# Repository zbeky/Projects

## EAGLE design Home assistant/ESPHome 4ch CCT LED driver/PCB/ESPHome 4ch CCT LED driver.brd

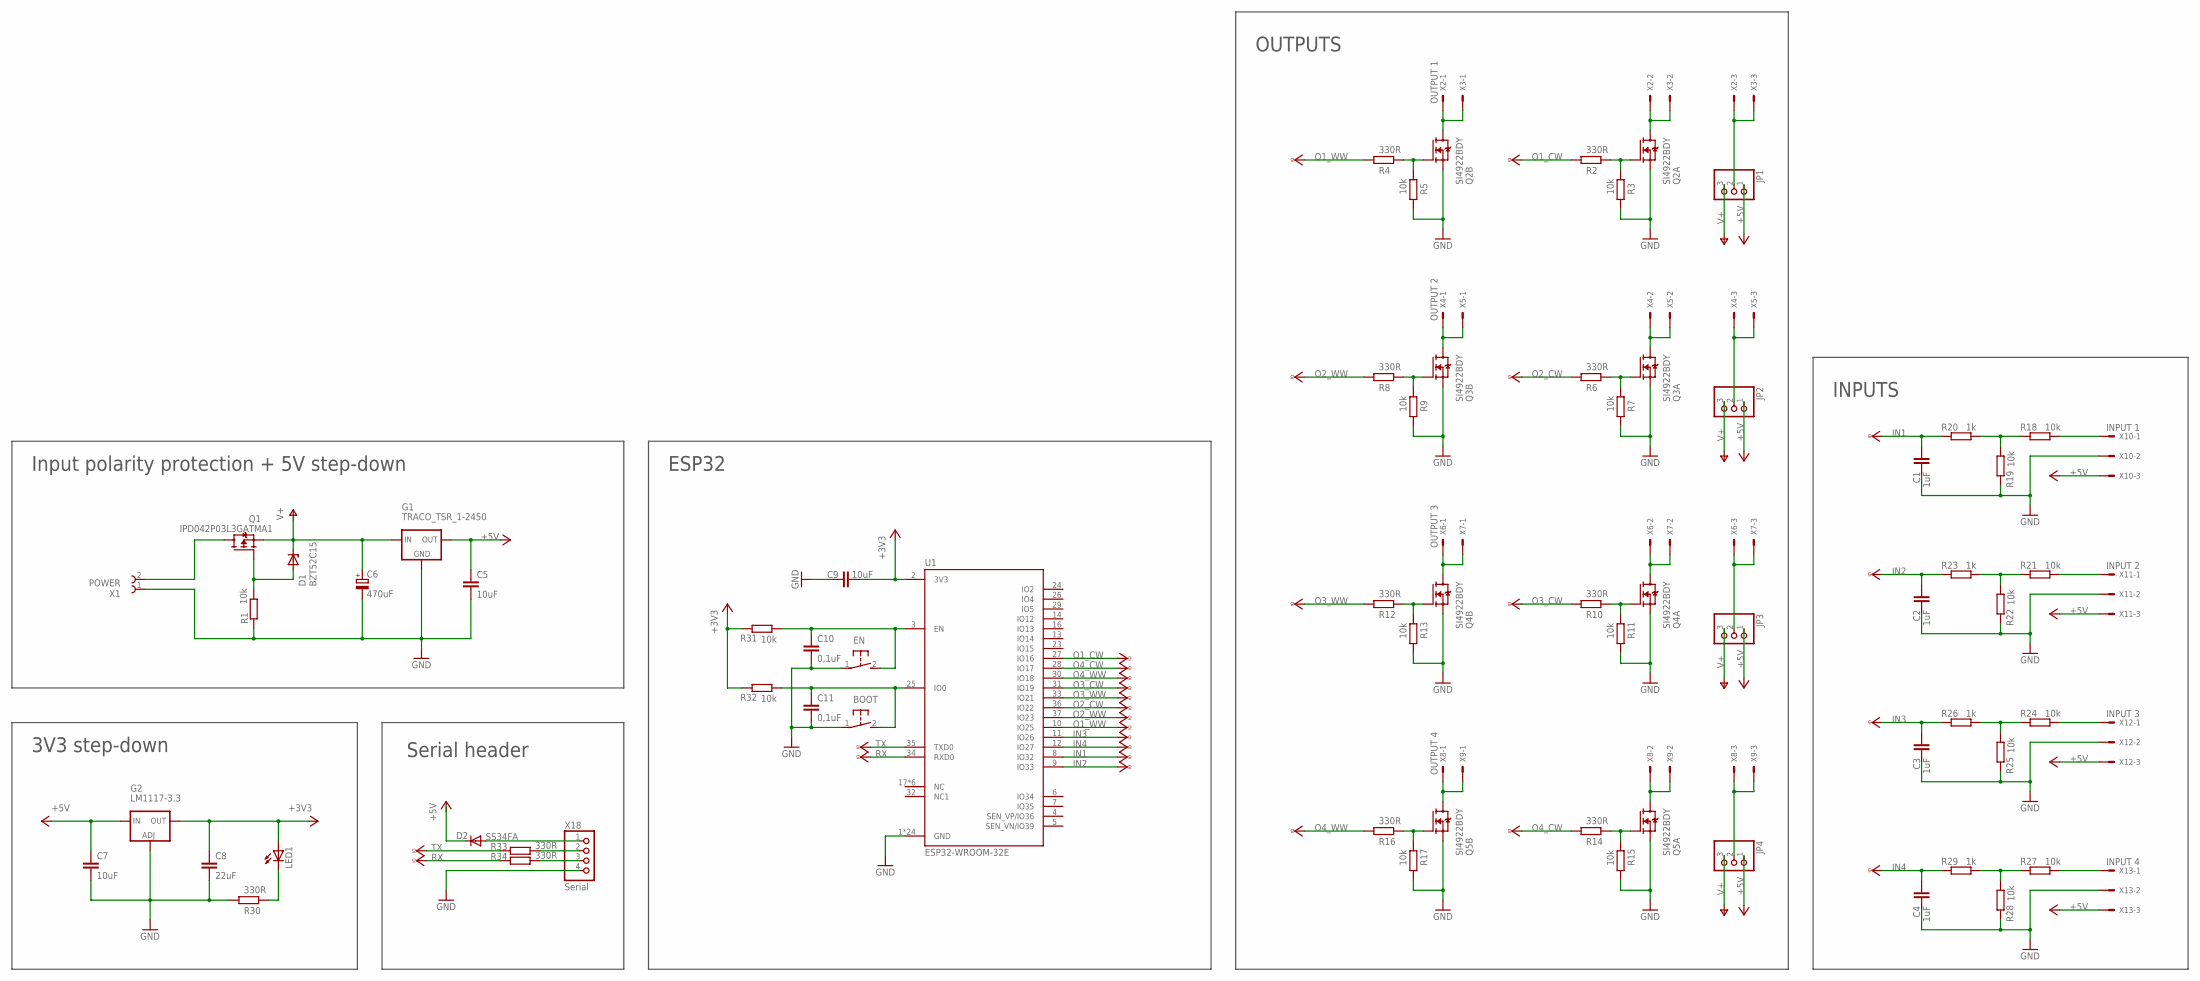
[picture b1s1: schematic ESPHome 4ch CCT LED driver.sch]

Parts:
BOOT: DTSM-3
C1, C2, C3, C4: 1uF; C1206
C5, C7, C9: 10uF; C1206
C6: 470uF; E5-10,5
C8: 22uF; C1206
C10, C11: 0,1uF; C0603
D1: BZT52C15; SOD123
D2: SS34FA; SOD123
EN: DTSM-3
G1: TRACO_TSR_1-2450; TRACO_TSR_1-24XX
G2: LM1117-3.3; SOT223
JP1, JP2, JP3, JP4: PINHD-1X3; 1X03
LED1: LEDCHIPLED_1206; CHIPLED_1206
Q1: IPD042P03L3GATMA1; TO252
Q2, Q3, Q4, Q5: SI4922BDY; SO-8
R1, R3, R5, R7, R9, R11, R13, R15, R17, R18, R19, R21, R22, R24, R25, R27, R28, R31, R32: 10k; R0805
R2, R4, R6, R8, R10, R12, R14, R16, R30, R33, R34: 330R; R0805
R20, R23, R26, R29: 1k; R0805
U1: ESP32-WROOM-32E; XCVR_ESP32-WROOM-32E_(16MB)
X1: POWER; 2PIN_5MM_TERMMINAL
X2: OUTPUT 1; JST-XH-03-PACKAGE-LONG-PAD
X3, X5, X7, X9: JST-XH-03; JST-XH-03-PACKAGE-LONG-PAD
X4: OUTPUT 2; JST-XH-03-PACKAGE-LONG-PAD
X6: OUTPUT 3; JST-XH-03-PACKAGE-LONG-PAD
X8: OUTPUT 4; JST-XH-03-PACKAGE-LONG-PAD
X10: INPUT 1; JST-XH-03-PACKAGE-LONG-PAD
X11: INPUT 2; JST-XH-03-PACKAGE-LONG-PAD
X12: INPUT 3; JST-XH-03-PACKAGE-LONG-PAD
X13: INPUT 4; JST-XH-03-PACKAGE-LONG-PAD
X18: Serial; 1X04

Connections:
+3V3: C8.1, C9.1, G2.2 (OUT), G2.4 (OUT), LED1.A, R31.1, R32.1, U1.2 (3V3)
+5V: C5.1, C7.1, D2.C, G1.VOUT (OUT), G2.3 (IN), JP1.1, JP2.1, JP3.1, JP4.1, X10.3, X11.3, X12.3, X13.3
GND: BOOT.1, C1.2, C2.2, C3.2, C4.2, C5.2, C6.-, C7.2, C8.2, C9.2, C10.2, C11.2, EN.1, G1.GND, G2.1 (ADJ), Q2.1 (S), Q2.3 (S), Q3.1 (S), Q3.3 (S), Q4.1 (S), Q4.3 (S), Q5.1 (S), Q5.3 (S), R1.1, R3.2, R5.2, R7.2, R9.2, R11.2, R13.2, R15.2, R17.2, R19.1, R22.1, R25.1, R28.1, R30.1, U1.1 (GND), U1.15 (GND), U1.38 (GND), U1.39_1 (GND), U1.39_2 (GND), U1.39_3 (GND), U1.39_4 (GND), U1.39_5 (GND), U1.39_6 (GND), U1.39_7 (GND), U1.39_8 (GND), U1.39_9 (GND), U1.39_10 (GND), U1.39_11 (GND), U1.39_12 (GND), U1.39_13 (GND), U1.39_14 (GND), U1.39_15 (GND), U1.39_16 (GND), U1.39_17 (GND), U1.39_18 (GND), U1.39_19 (GND), U1.39_20 (GND), U1.39_21 (GND), X1.1, X10.2, X11.2, X12.2, X13.2, X18.4
IN1: C1.1, R20.1, U1.8 (IO32)
IN2: C2.1, R23.1, U1.9 (IO33)
IN3: C3.1, R26.1, U1.11 (IO26)
IN4: C4.1, R29.1, U1.12 (IO27)
unnamed: R18.1, R19.2, R20.2
unnamed: Q2.4 (G), R4.2, R5.1
unnamed: R21.2, X11.1
unnamed: R21.1, R22.2, R23.2
unnamed: Q2.2 (G), R2.1, R3.1
unnamed: Q2.7 (D), Q2.8 (D), X2.2, X3.2
unnamed: D1.A, Q1.1 (G), R1.2
unnamed: BOOT.2, C11.1, R32.2, U1.25 (IO0)
unnamed: Q3.5 (D), Q3.6 (D), X4.1, X5.1
unnamed: Q2.5 (D), Q2.6 (D), X2.1, X3.1
unnamed: Q3.4 (G), R8.2, R9.1
unnamed: Q3.2 (G), R6.1, R7.1
unnamed: JP4.2, X8.3, X9.3
unnamed: Q3.7 (D), Q3.8 (D), X4.2, X5.2
unnamed: JP3.2, X6.3, X7.3
unnamed: Q4.4 (G), R12.2, R13.1
unnamed: Q4.2 (G), R10.1, R11.1
unnamed: JP2.2, X4.3, X5.3
unnamed: Q4.7 (D), Q4.8 (D), X6.2, X7.2
unnamed: Q4.5 (D), Q4.6 (D), X6.1, X7.1
unnamed: Q5.4 (G), R16.2, R17.1
unnamed: Q5.2 (G), R14.1, R15.1
unnamed: JP1.2, X2.3, X3.3
unnamed: Q5.7 (D), Q5.8 (D), X8.2, X9.2
unnamed: Q5.5 (D), Q5.6 (D), X8.1, X9.1
unnamed: R24.2, X12.1
unnamed: R24.1, R25.2, R26.2
unnamed: R18.2, X10.1
unnamed: R27.2, X13.1
unnamed: R27.1, R28.2, R29.2
unnamed: Q1.3 (D), X1.2
unnamed: LED1.C, R30.2
unnamed: C10.1, EN.2, R31.2, U1.3 (EN)
unnamed: D2.A, X18.1
unnamed: R33.2, X18.2
unnamed: R34.2, X18.3
O1_CW: R2.2, U1.27 (IO16)
O1_WW: R4.1, U1.10 (IO25)
O2_CW: R6.2, U1.36 (IO22)
O2_WW: R8.1, U1.37 (IO23)
O3_CW: R10.2, U1.31 (IO19)
O3_WW: R12.1, U1.33 (IO21)
O4_CW: R14.2, U1.28 (IO17)
O4_WW: R16.1, U1.30 (IO18)
RX: R34.1, U1.34 (RXD0)
TX: R33.1, U1.35 (TXD0)
V+: C6.+, D1.C, G1.VIN (IN), JP1.3, JP2.3, JP3.3, JP4.3, Q1.2 (S)

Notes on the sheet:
Input polarity protection + 5V step-down
OUTPUTS
INPUTS
3V3 step-down
ESP32
Serial header

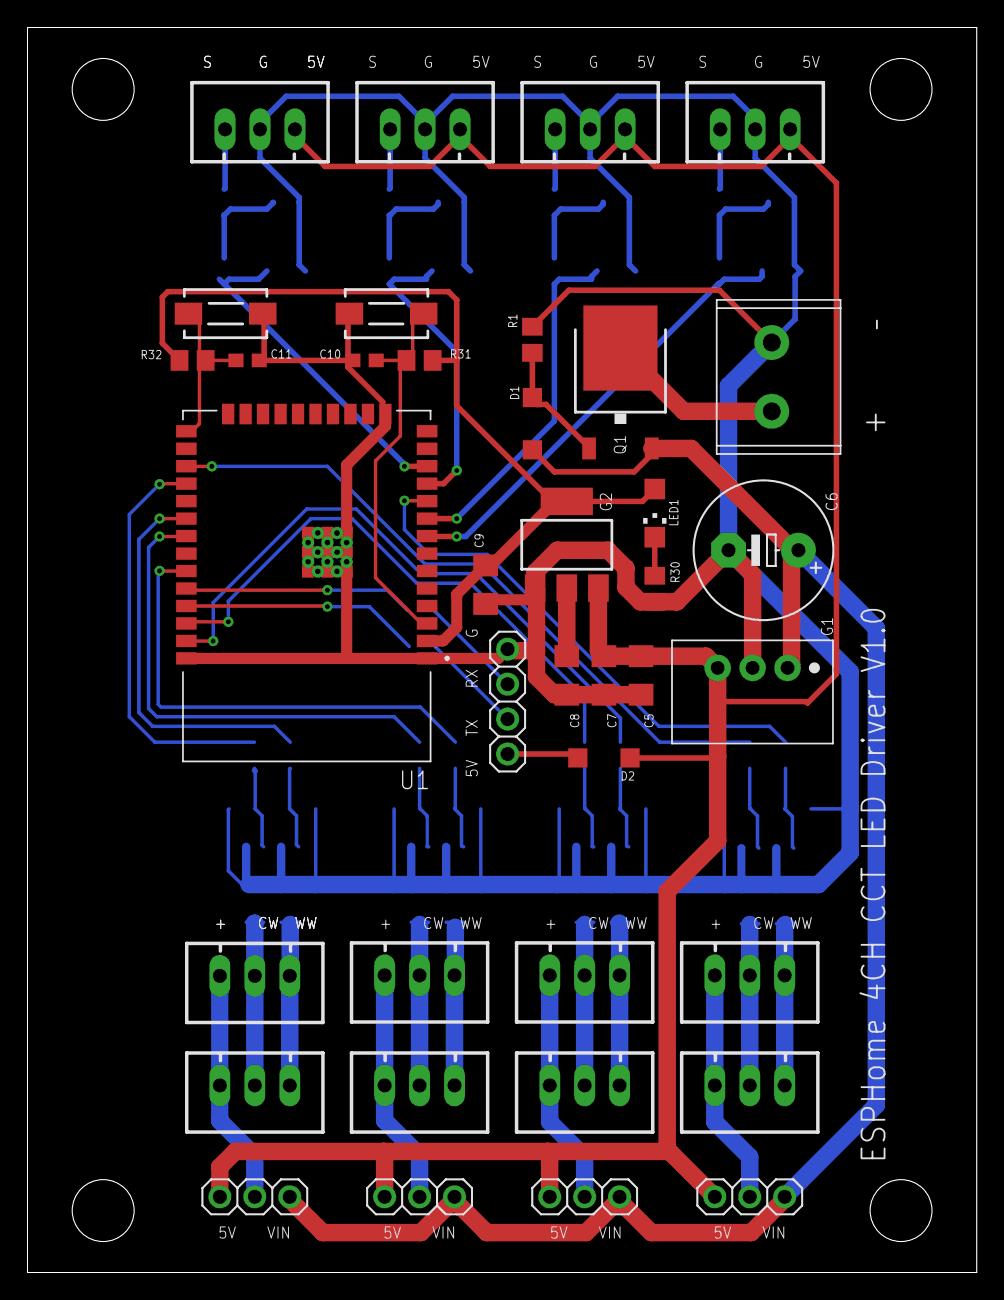
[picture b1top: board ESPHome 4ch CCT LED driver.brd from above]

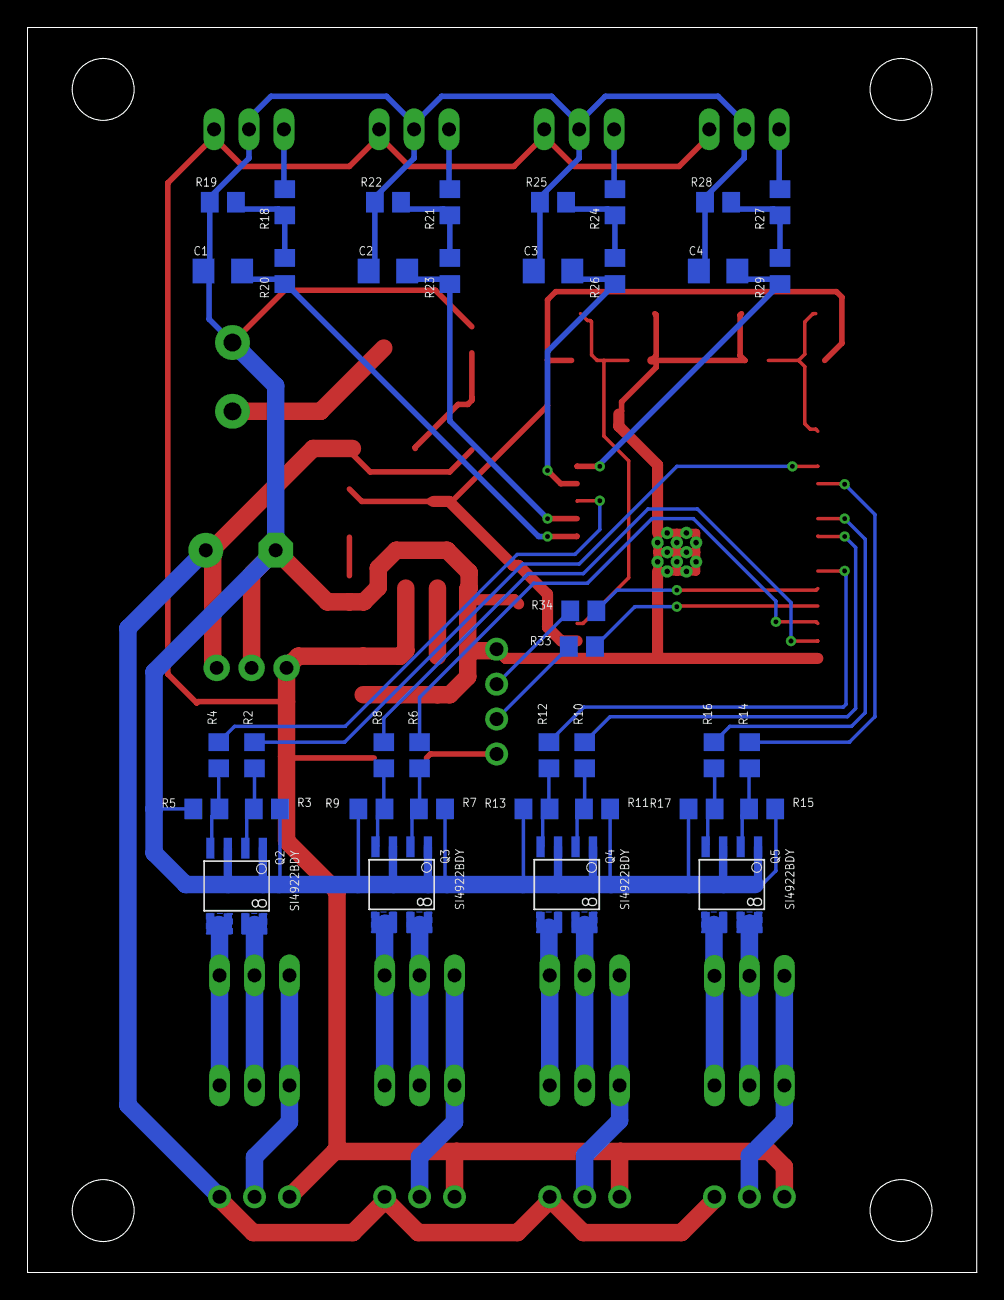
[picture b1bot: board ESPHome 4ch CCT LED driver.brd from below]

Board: 2 copper layers, 69.0 x 90.5 mm, 76 parts (38 on the bottom side), 54 nets.

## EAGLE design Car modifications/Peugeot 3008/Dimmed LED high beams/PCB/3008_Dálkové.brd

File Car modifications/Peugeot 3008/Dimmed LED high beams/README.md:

# Peugeot 3008 aftermarket LED high beams dimmig

- Adjustable current source with switch to voltage source<br><br>

- When headlights are turned on, high beams will have low brightness (current limiting of LED)
- When high beams are turned on, also headlight will turn on on full brightness

## Additional parts:<br>
4 pieces 9006 connector set<br>
2 pieces step up voltage regulator Pololu U3V70F15 -https://www.pololu.com/product/2896<br>
2 pieces diode 10A10 to block voltage going from high beam through main beams back to ECU

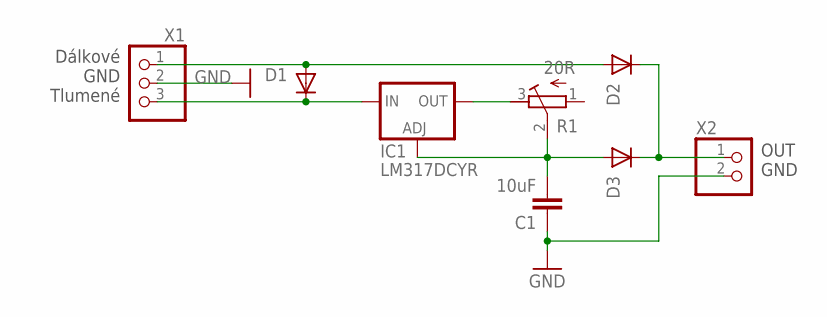
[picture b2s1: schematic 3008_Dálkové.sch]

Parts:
C1: 10uF; C1210
D1, D2, D3: DIODE-DO214AA; DO214AA
IC1: LM317DCYR; SOT223
R1: 20R; 3362P
X1: PINHD-1X3; 1X03
X2: PINHD-1X2; 1X02

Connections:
DALK_IN: D1.A, D2.A, X1.1
DALK_OUT: D2.C, D3.C, X2.1
GND: C1.1, X1.2, X2.2
unnamed: IC1.2 (OUT), IC1.4 (OUT), R1.3 (E)
REGUL: C1.2, D3.A, IC1.1 (ADJ), R1.2 (S)
TLUM_IN: D1.C, IC1.3 (IN), X1.3

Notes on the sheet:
Dálkové GND Tlumené
OUT GND

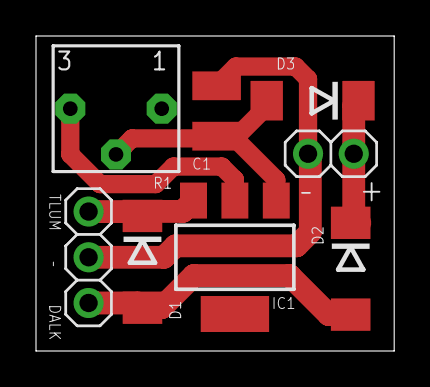
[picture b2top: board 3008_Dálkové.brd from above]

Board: 2 copper layers, 19.9 x 17.5 mm, 8 parts (0 on the bottom side), 6 nets.

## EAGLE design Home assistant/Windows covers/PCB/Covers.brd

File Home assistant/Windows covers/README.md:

# Automatic window blinds

Body can be printed from PLA, PETG, ABS, etc.

## Additional parts:<br>
1 piece ESP32-WROOM-32D - https://www.aliexpress.com/item/32959541446.html<br>
2 pieces hall sensor rotary sensor - https://www.aliexpress.com/item/4000170678550.html<br>
2 pieces mini XLR 5 pin connector - https://www.aliexpress.com/item/4000105190839.html<br>
2 pieces 4mm-6mm coupler - https://www.aliexpress.com/item/4000194793728.html<br>
2 pieces 3mm-4mm coupler - https://www.aliexpress.com/item/4000194793728.html<br>

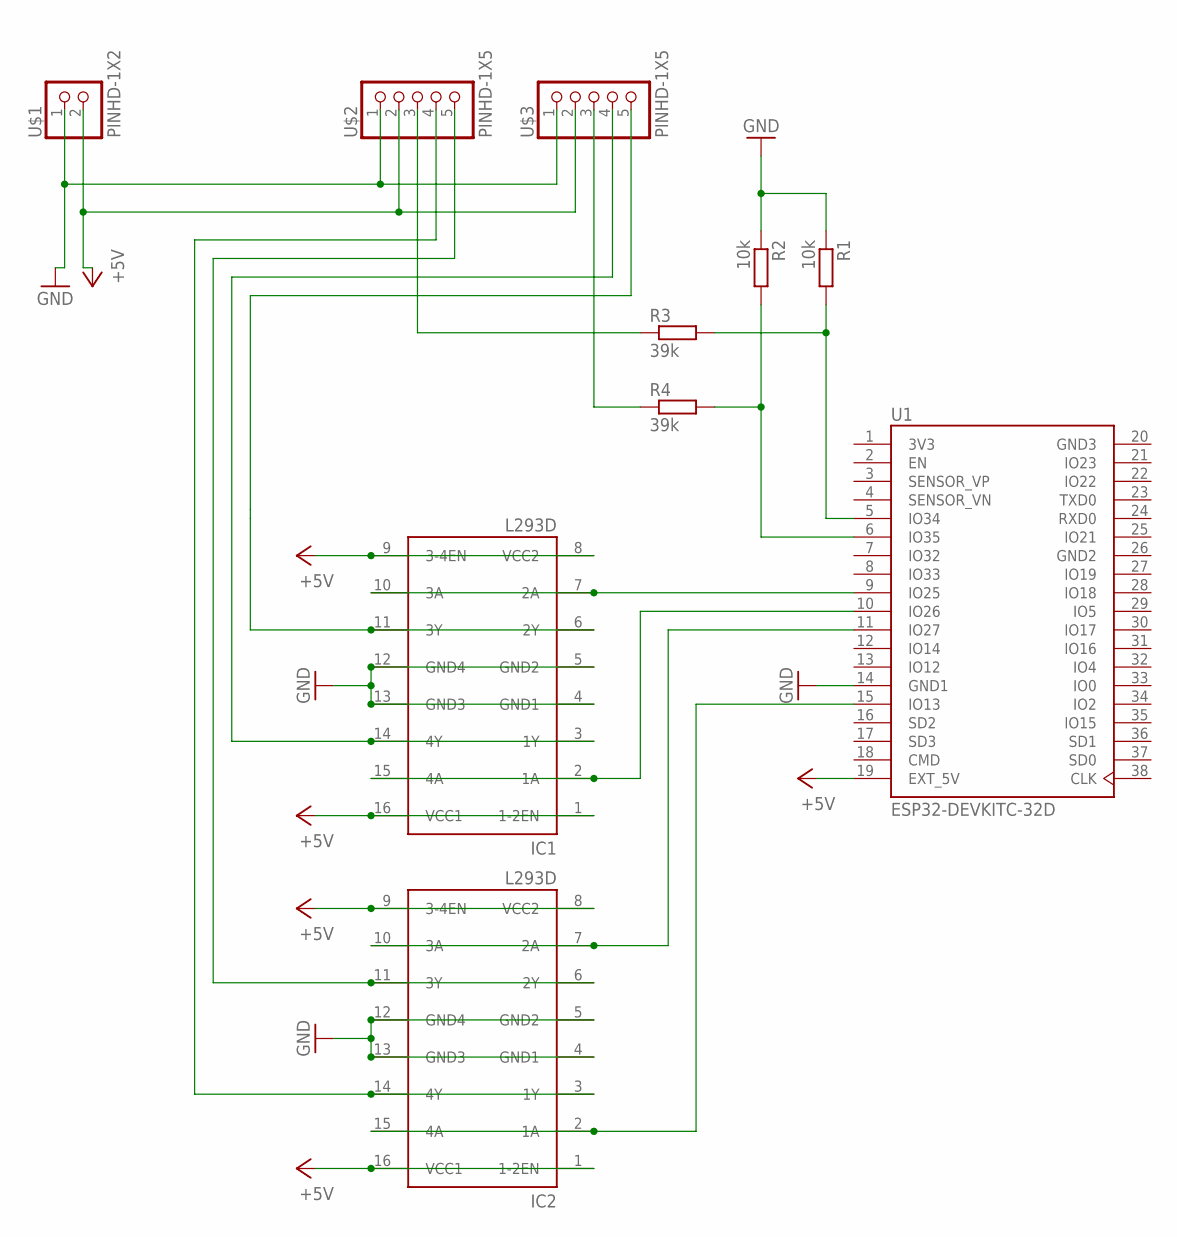
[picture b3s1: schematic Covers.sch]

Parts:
IC1, IC2: L293D; DIL16
R1, R2: 10k; 0207/10
R3, R4: 39k; 0207/10
U1: ESP32-DEVKITC-32D; MODULE_ESP32-DEVKITC-32D
U$1: PINHD-1X2; 1X02
U$2, U$3: PINHD-1X5; 1X05

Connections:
3V3: U1.1 (3V3)
+5V: IC1.1 (1-2EN), IC1.8 (VCC2), IC1.9 (3-4EN), IC1.16 (VCC1), IC2.1 (1-2EN), IC2.8 (VCC2), IC2.9 (3-4EN), IC2.16 (VCC1), U1.19 (EXT_5V), U$1.2, U$2.2, U$3.2
GND: IC1.4 (GND1), IC1.5 (GND2), IC1.12 (GND4), IC1.13 (GND3), IC2.4 (GND1), IC2.5 (GND2), IC2.12 (GND4), IC2.13 (GND3), R1.1, R2.1, U1.14 (GND1), U$1.1, U$2.1, U$3.1
GND2: U1.26 (GND2)
GND3: U1.20 (GND3)
unnamed: IC1.2 (1A), IC1.15 (4A), U1.10 (IO26)
unnamed: IC1.6 (2Y), IC1.11 (3Y), U$3.5
unnamed: IC2.6 (2Y), IC2.11 (3Y), U$2.5
unnamed: IC1.3 (1Y), IC1.14 (4Y), U$3.4
unnamed: R2.2, R4.2, U1.6 (IO35)
unnamed: R1.2, R3.2, U1.5 (IO34)
unnamed: R4.1, U$3.3
unnamed: R3.1, U$2.3
unnamed: IC2.3 (1Y), IC2.14 (4Y), U$2.4
unnamed: IC2.2 (1A), IC2.15 (4A), U1.15 (IO13)
unnamed: IC1.7 (2A), IC1.10 (3A), U1.9 (IO25)
unnamed: IC2.7 (2A), IC2.10 (3A), U1.11 (IO27)

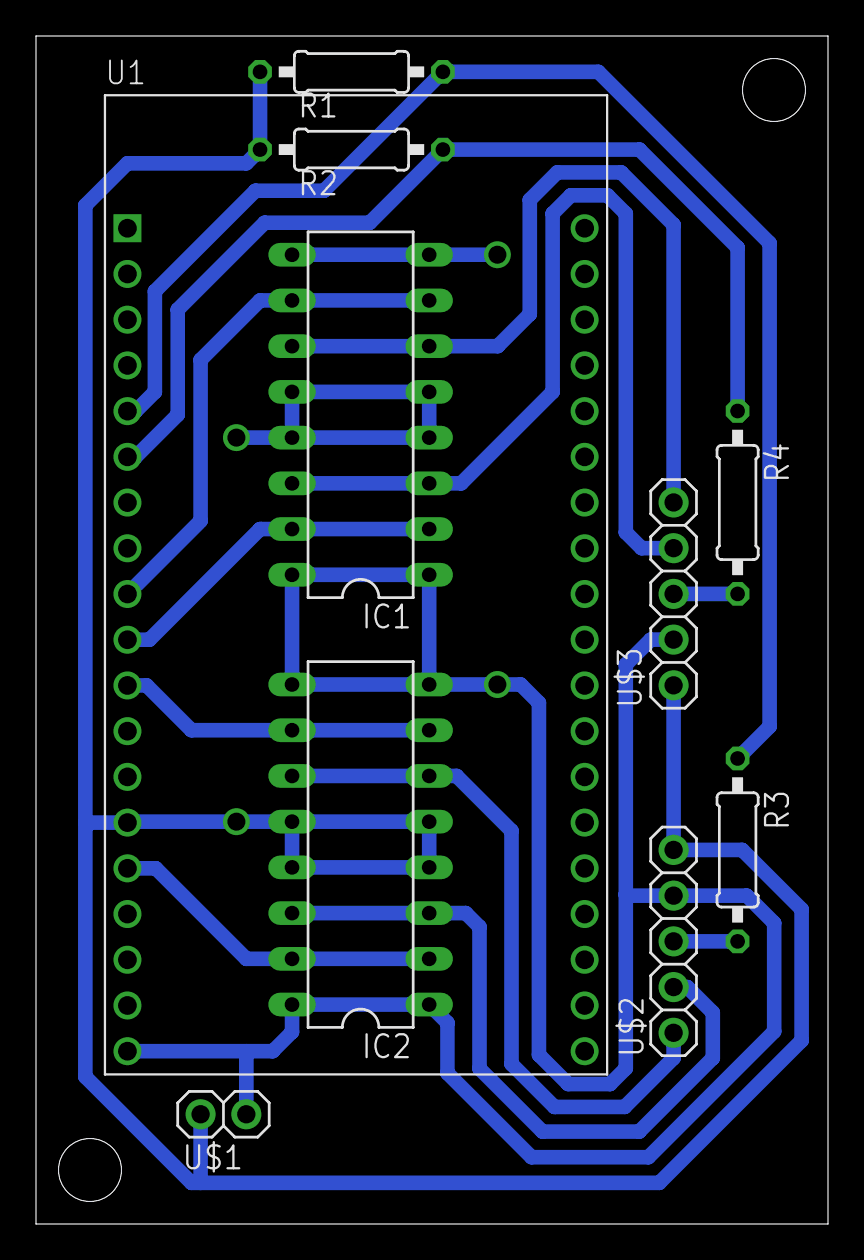
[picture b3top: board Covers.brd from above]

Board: 2 copper layers, 44.0 x 66.0 mm, 10 parts (0 on the bottom side), 14 nets.

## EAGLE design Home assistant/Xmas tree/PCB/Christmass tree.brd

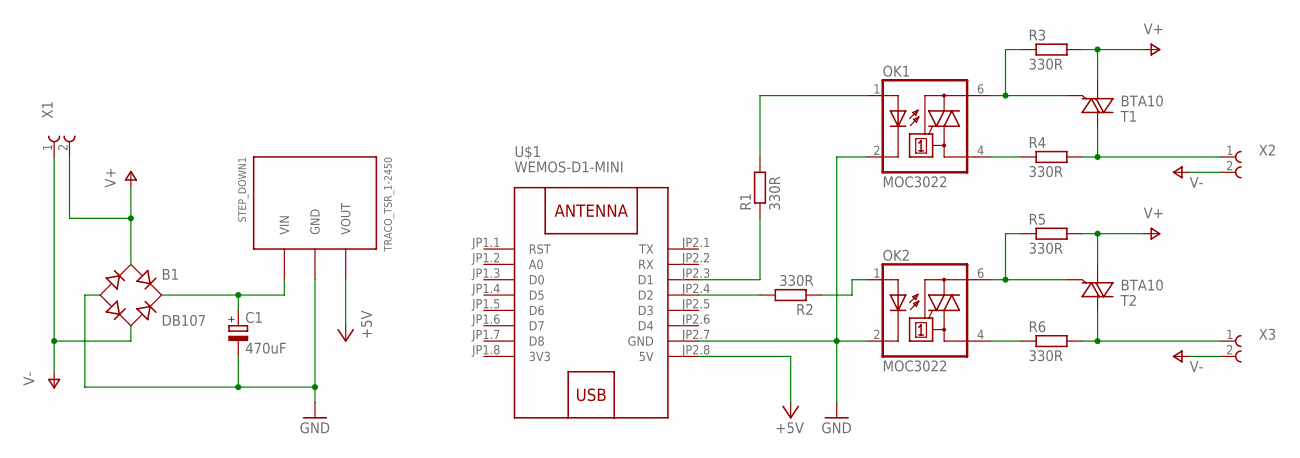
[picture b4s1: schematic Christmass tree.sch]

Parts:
B1: DB107; DB
C1: 470uF; E5-10,5
OK1, OK2: MOC3022; DIL06
R1, R2, R3, R4, R5, R6: 330R; 0204/7
STEP_DOWN1: TRACO_TSR_1-2450
T1, T2: BTA10; TO218DS
U$1: WEMOS-D1-MINI; WEMOS-D1-MINI_BEZ
X1, X2, X3: 2PIN_5MM_TERMINAL; 2PIN_5MM_TERMMINAL

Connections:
3V3: U$1.JP1.8 (3V3)
+5V: STEP_DOWN1.VOUT, U$1.JP2.8 (5V)
GND: B1.-, C1.-, OK1.2 (C), OK2.2 (C), STEP_DOWN1.GND, U$1.JP2.7 (GND)
unnamed: OK2.1 (A), R2.1
unnamed: B1.+, C1.+, STEP_DOWN1.VIN
unnamed: R2.2, U$1.JP2.4 (D2)
unnamed: R1.1, U$1.JP2.3 (D1)
unnamed: OK1.1 (A), R1.2
unnamed: OK1.6 (A2), R3.1, T1.G
unnamed: OK2.6 (A2), R5.1, T2.G
unnamed: OK1.4 (A1), R4.1
unnamed: R4.2, T1.A2, X2.1
unnamed: OK2.4 (A1), R6.1
unnamed: R6.2, T2.A2, X3.1
V+: B1.AC1, R3.2, R5.2, T1.A1, T2.A1, X1.2
V-: B1.AC2, X1.1, X2.2, X3.2

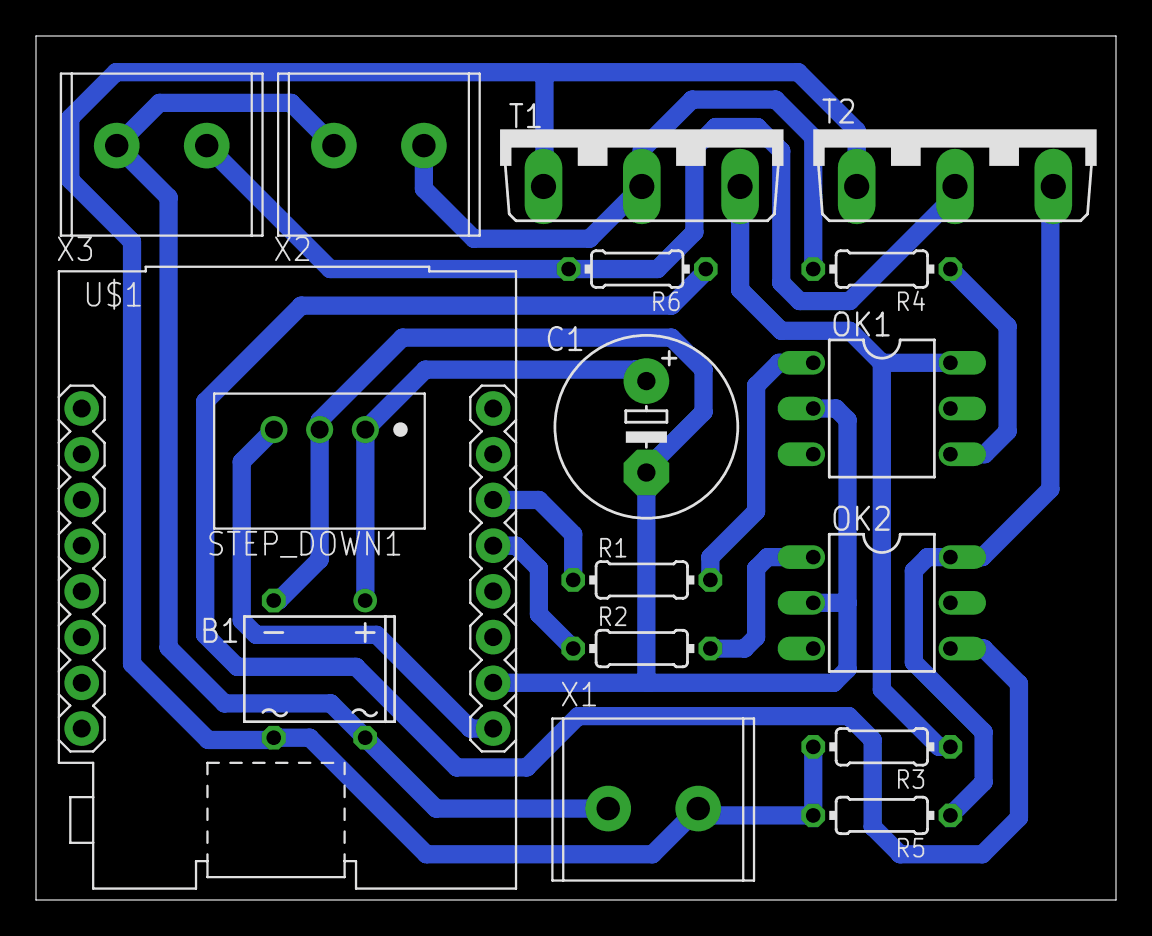
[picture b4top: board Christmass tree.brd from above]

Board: 2 copper layers, 60.0 x 48.0 mm, 17 parts (0 on the bottom side), 15 nets.

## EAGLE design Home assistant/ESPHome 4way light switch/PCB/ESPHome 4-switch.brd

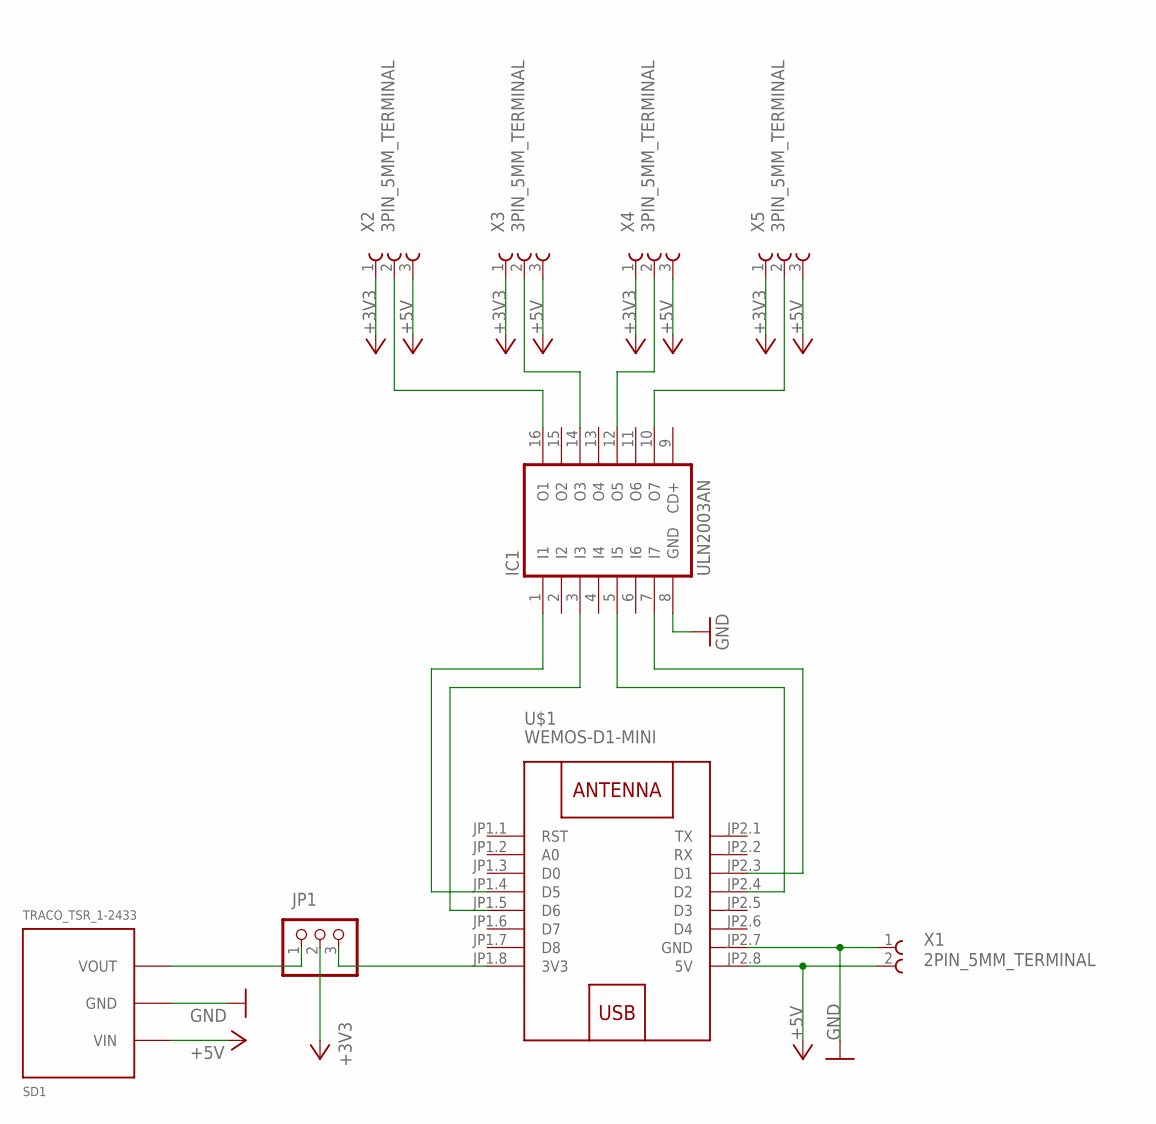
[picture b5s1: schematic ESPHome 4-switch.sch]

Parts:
IC1: ULN2003AN; DIL16
JP1: PINHD-1X3; 1X03
SD1: TRACO_TSR_1-2433; TRACO_TSR_1-24XX
U$1: WEMOS-D1-MINI
X1: 2PIN_5MM_TERMINAL; 2PIN_5MM_TERMMINAL
X2, X3, X4, X5: 3PIN_5MM_TERMINAL

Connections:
+3V3: JP1.2, X2.1, X3.1, X4.1, X5.1
+5V: SD1.VIN, U$1.JP2.8 (5V), X1.2, X2.3, X3.3, X4.3, X5.3
GND: IC1.8 (GND), SD1.GND, U$1.JP2.7 (GND), X1.1
unnamed: JP1.1, SD1.VOUT
unnamed: JP1.3, U$1.JP1.8 (3V3)
unnamed: IC1.5 (I5), U$1.JP2.4 (D2)
unnamed: IC1.7 (I7), U$1.JP2.3 (D1)
unnamed: IC1.3 (I3), U$1.JP1.5 (D6)
unnamed: IC1.1 (I1), U$1.JP1.4 (D5)
unnamed: IC1.16 (O1), X2.2
unnamed: IC1.14 (O3), X3.2
unnamed: IC1.12 (O5), X4.2
unnamed: IC1.10 (O7), X5.2

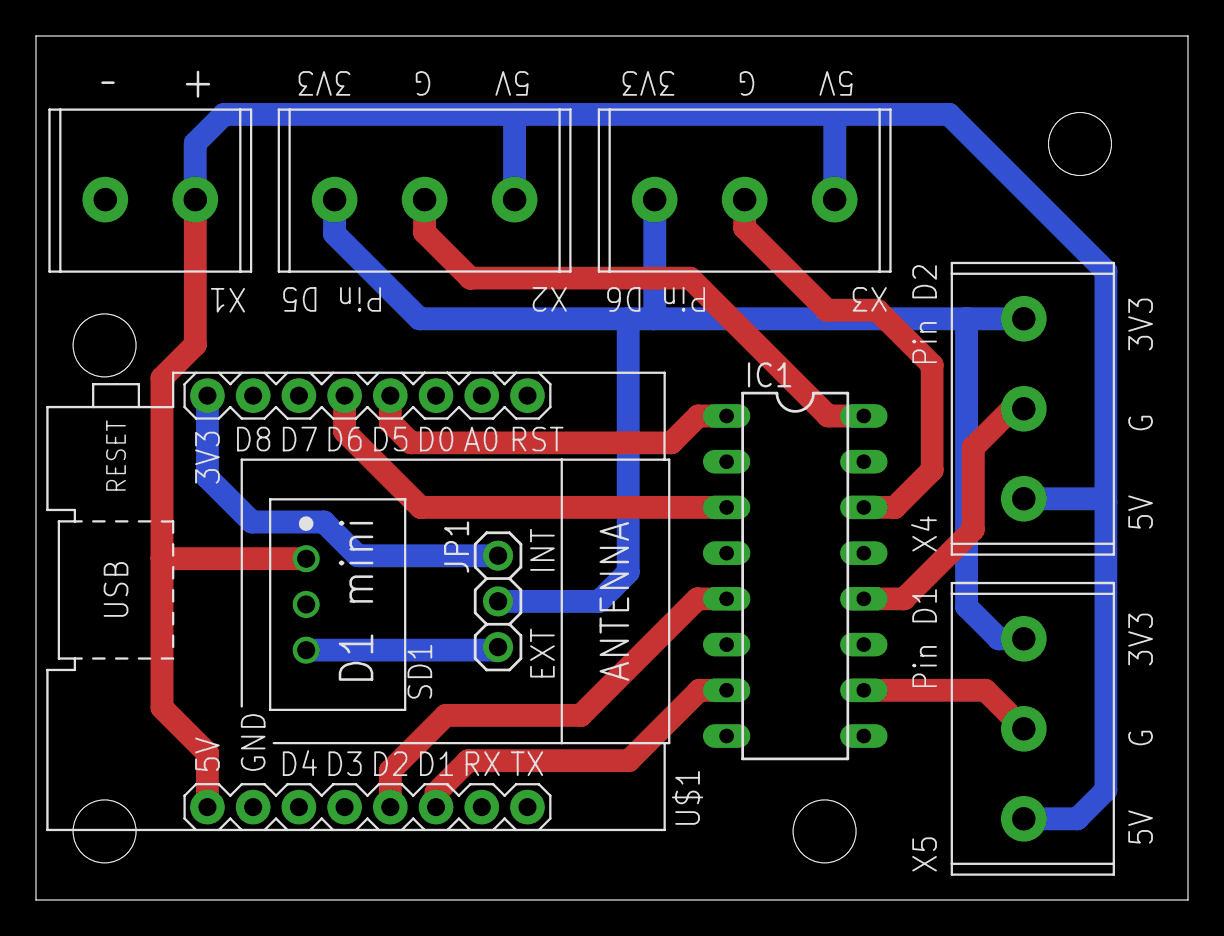
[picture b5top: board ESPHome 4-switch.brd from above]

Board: 2 copper layers, 64.0 x 48.0 mm, 9 parts (0 on the bottom side), 13 nets.

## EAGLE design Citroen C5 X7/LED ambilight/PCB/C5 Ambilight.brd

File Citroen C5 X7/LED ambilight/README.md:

# Citroen C5 X7 dual light ambilight

Strong warm white light when doors are opened

Dimmed red light when headlights are on

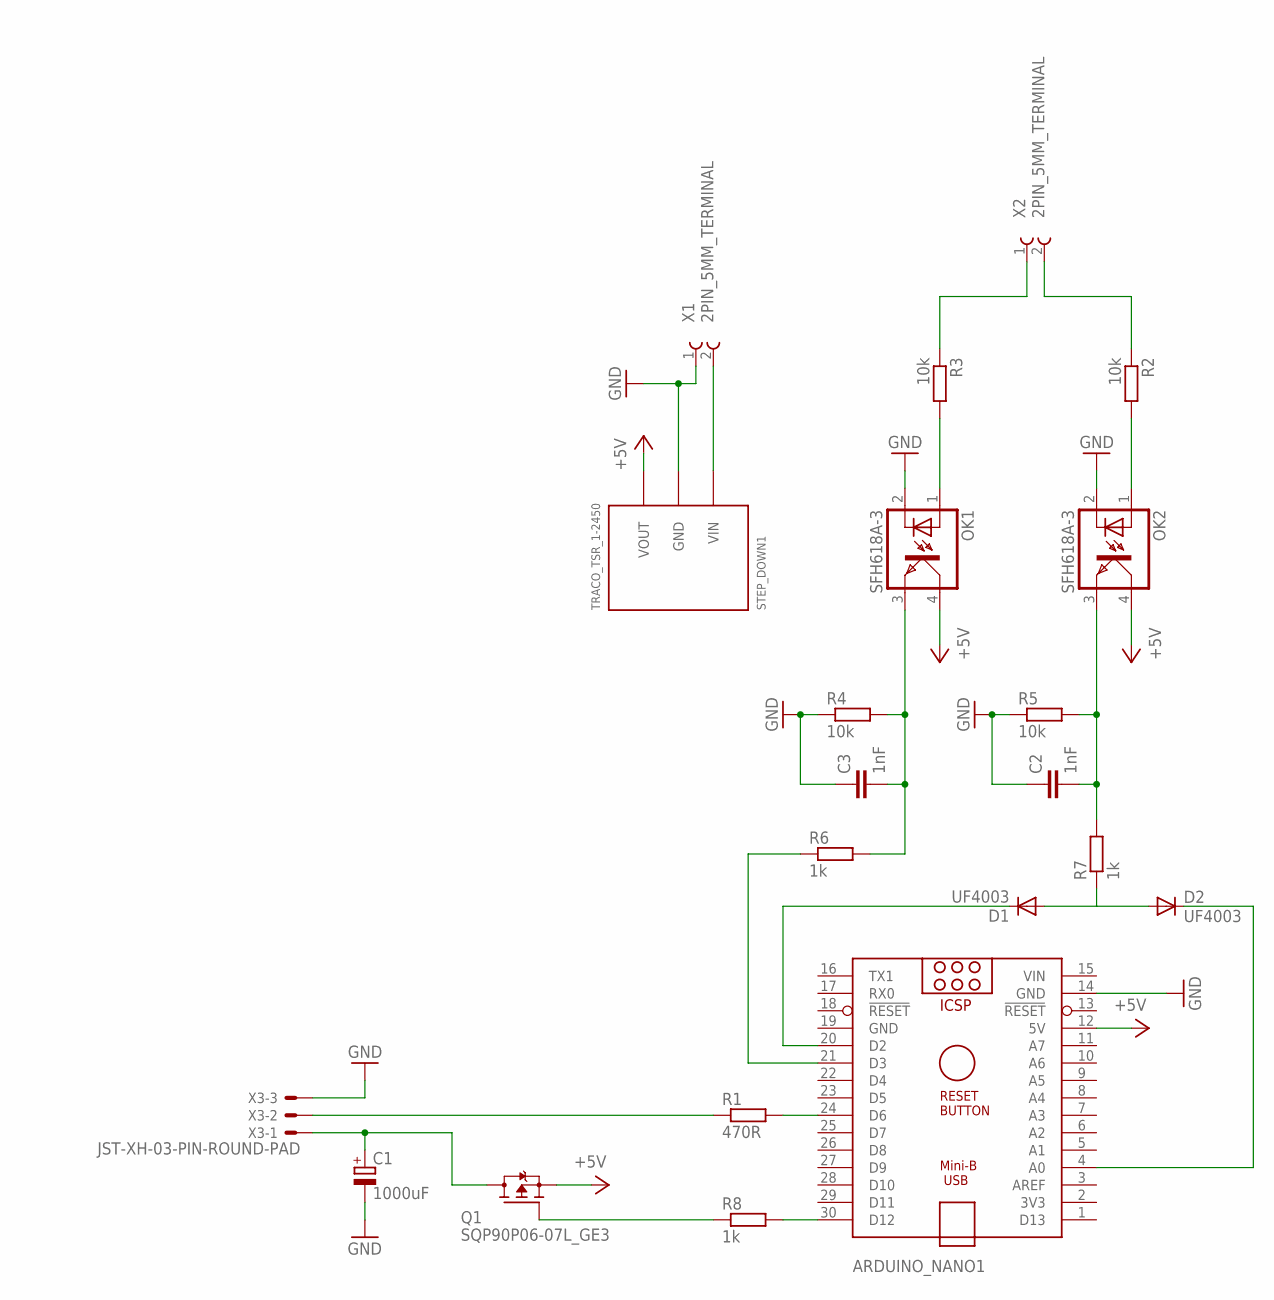
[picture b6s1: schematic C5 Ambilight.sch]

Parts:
ARDUINO_NANO1: ARDUINO_NANO
C1: 1000uF; TT5D10
C2, C3: 1nF; C050-025X075
D1, D2: UF4003; DO41-10
OK1, OK2: SFH618A-3; DIP4
Q1: SQP90P06-07L_GE3; TO220V
R1: 470R; 0207/10
R2, R3: 10k; 0207/7
R4, R5: 10k; 0207/10
R6, R7, R8: 1k; 0207/10
STEP_DOWN1: TRACO_TSR_1-2450
X1, X2: 2PIN_5MM_TERMINAL; 2PIN_5MM_TERMMINAL
X3: JST-XH-03-PIN-ROUND-PAD; JST-XH-03-PACKAGE-ROUND-PAD

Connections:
5V_LED: C1.+, Q1.2 (D), X3.1
12V: STEP_DOWN1.VIN, X1.2
+5V: ARDUINO_NANO1.12 (5V), OK1.4 (COL), OK2.4 (COL), Q1.3 (S), STEP_DOWN1.VOUT
GND: ARDUINO_NANO1.14 (GND), ARDUINO_NANO1.19 (GND), C1.-, C2.1, C3.1, OK1.2 (C), OK2.2 (C), R4.1, R5.1, STEP_DOWN1.GND, X1.1, X3.3
unnamed: ARDUINO_NANO1.30 (D12), R8.2
unnamed: ARDUINO_NANO1.24 (D6), R1.2
unnamed: R2.1, X2.2
unnamed: R1.1, X3.2
unnamed: R3.1, X2.1
unnamed: OK1.1 (A), R3.2
unnamed: OK2.1 (A), R2.2
unnamed: C3.2, OK1.3 (EMIT), R4.2, R6.2
unnamed: C2.2, OK2.3 (EMIT), R5.2, R7.2
unnamed: Q1.1 (G), R8.1
unnamed: ARDUINO_NANO1.21 (D3), R6.1
unnamed: ARDUINO_NANO1.20 (D2), D1.C
unnamed: ARDUINO_NANO1.4 (A0), D2.C
unnamed: D1.A, D2.A, R7.1
VIN: ARDUINO_NANO1.15 (VIN)

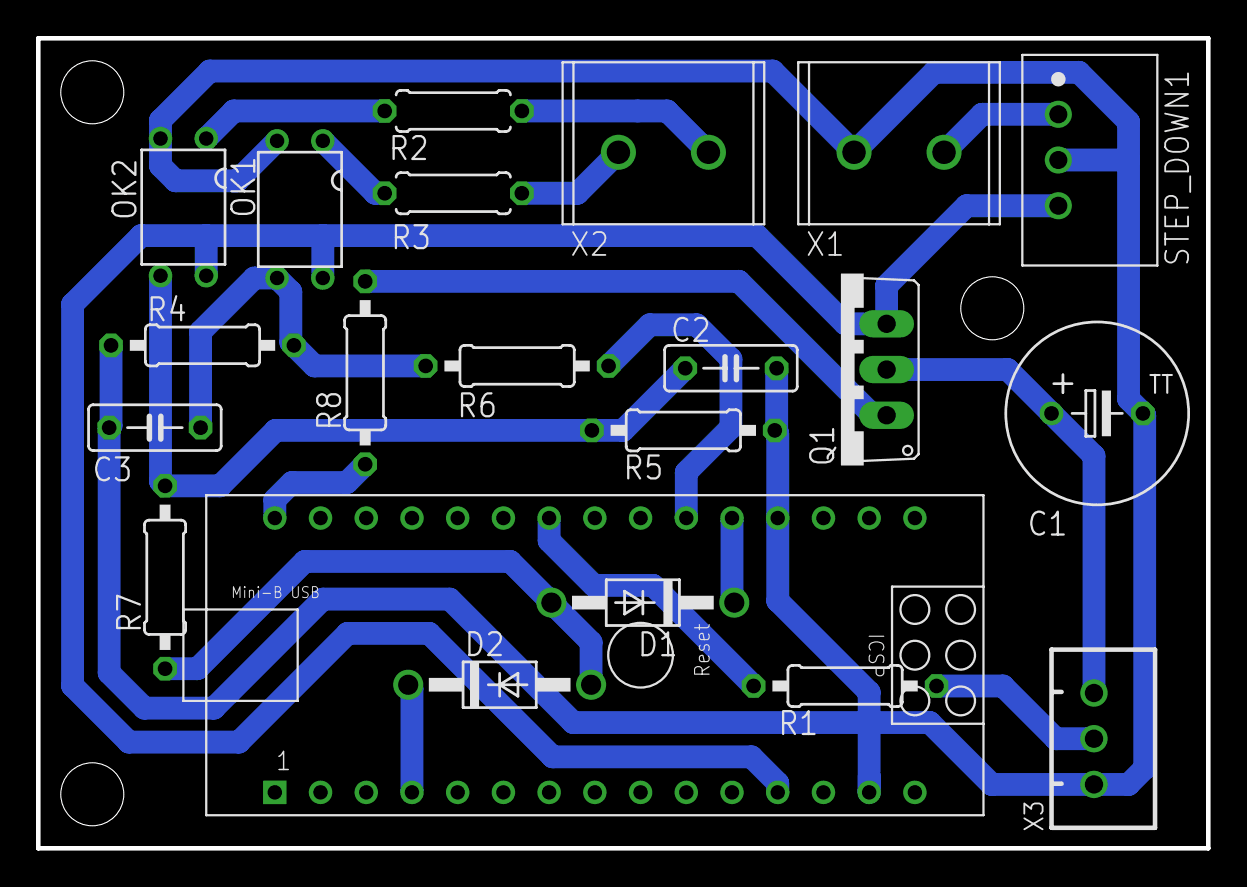
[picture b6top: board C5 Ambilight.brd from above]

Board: 2 copper layers, 65.0 x 45.0 mm, 21 parts (0 on the bottom side), 18 nets.

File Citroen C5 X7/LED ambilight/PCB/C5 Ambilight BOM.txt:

Partlist exported from //cz-prl-ns-17.kiekert.com/User-Documents/senkerikm/EAGLE/projects/Doma/C5 Ambilight/C5 Ambilight.sch at 13.11.2020 7:03

Part          Value                   Device                    Package                     Description                                            
ARDUINO_NANO1                         ARDUINO_NANO              ARDUINO_NANO                Arduino Nano V3.0                                      
C1            1000uF                  CPOL-EUTT5D10             TT5D10                      POLARIZED CAPACITOR, European symbol                   
C2            1nF                     C-EU050-025X075           C050-025X075                CAPACITOR, European symbol                             
C3            1nF                     C-EU050-025X075           C050-025X075                CAPACITOR, European symbol                             
D1            UF4003                  UF4003                    DO41-10                     DIODE                                                  
D2            UF4003                  UF4003                    DO41-10                     DIODE                                                  
OK1           SFH618A-3               SFH618A-3                 DIP4                        Optocoupler, Phototransistor Output, Low Input Current 
OK2           SFH618A-3               SFH618A-3                 DIP4                        Optocoupler, Phototransistor Output, Low Input Current 
Q1            SQP90P06-07L_GE3        VISHAY_SQP90P06-07LTO220V TO220V                                                                             
R1            470R                    R-EU_0207/10              0207/10                     RESISTOR, European symbol                              
R2            10k                     R-EU_0207/7               0207/7                      RESISTOR, European symbol                              
R3            10k                     R-EU_0207/7               0207/7                      RESISTOR, European symbol                              
R4            10k                     R-EU_0207/10              0207/10                     RESISTOR, European symbol                              
R5            10k                     R-EU_0207/10              0207/10                     RESISTOR, European symbol                              
R6            1k                      R-EU_0207/10              0207/10                     RESISTOR, European symbol                              
R7            1k                      R-EU_0207/10              0207/10                     RESISTOR, European symbol                              
R8            1k                      R-EU_0207/10              0207/10                     RESISTOR, European symbol                              
STEP_DOWN1    TRACO_TSR_1-2450        TRACO_TSR_1-2450          TRACO_TSR_1-2450                                                                   
X1            2PIN_5MM_TERMINAL       2PIN_5MM_TERMINAL         2PIN_5MM_TERMMINAL                                                                 
X2            2PIN_5MM_TERMINAL       2PIN_5MM_TERMINAL         2PIN_5MM_TERMMINAL                                                                 
X3            JST-XH-03-PIN-ROUND-PAD JST-XH-03-PIN-ROUND-PAD   JST-XH-03-PACKAGE-ROUND-PAD JST XH Connector 2 Pin

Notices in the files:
parts and their libraries:
Sbirka modulu: Released under the Creative Commons Attribution 4.0 International License: http://creativecommons.org/licenses/by/4.0
